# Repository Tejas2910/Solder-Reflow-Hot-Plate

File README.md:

# Solder-Reflow-Hot-Plate
## Course Project EE344: Electronic Design Lab

Project Details:
 -  Recipient of Best Project Award in the Electrical Engineering Department among 200+ students for creating Solder Reflow Hot Plate instrument to solder SMD components 
 -  Engineered a high-performance heating element reaching temperatures up to 300°C, a cooling mechanism capable
    of dropping temperatures at a maximum rate of 3°C/s, and a precision feedback circuit for temperature control
 -  Collaborated within a 3-member team to design an intuitive web interface for configuring reflow profiles, a user-
    friendly TFT LCD display for real-time information, a 3D-printed enclosure and PCB layouts using Eagle

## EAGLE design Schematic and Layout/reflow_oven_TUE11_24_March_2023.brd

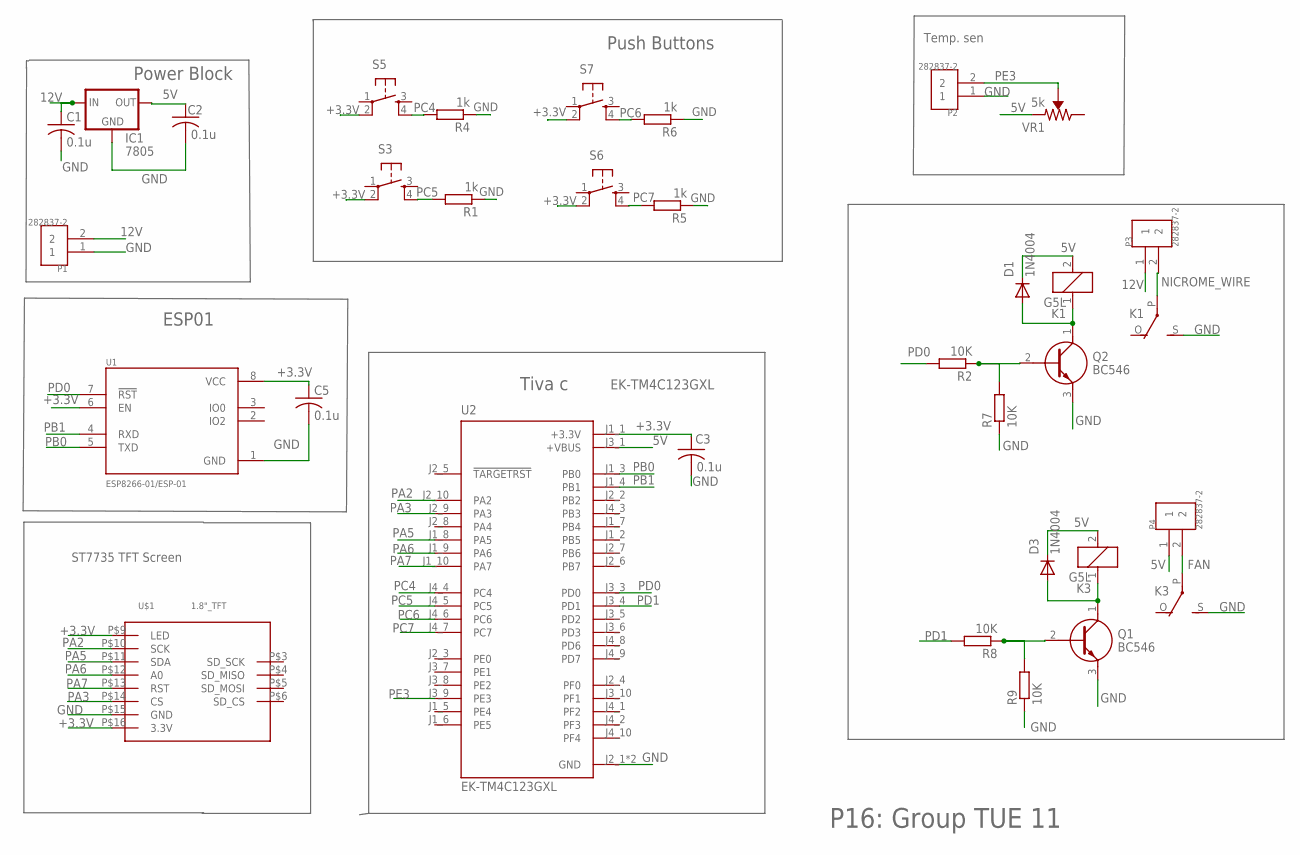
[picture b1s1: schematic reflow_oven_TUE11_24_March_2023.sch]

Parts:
C1, C2, C3, C5: 0.1u; C1206
D1, D3: 1N4004; DO41-10
IC1: 7805; 78XXS
K1, K3: G5L; G5LE
P1, P2, P3, P4: 282837-2; TE_282837-2
Q1, Q2: BC546
R1, R4, R5, R6: 1k; R1206
R2, R7, R8, R9: 10K; R1206
S3, S5, S6, S7: TAC_SWITCHPTH; TACTILE-PTH
U1: ESP8266-01/ESP-01; XCVR_ESP8266-01/ESP-01
U2: EK-TM4C123GXL; MODULE_EK-TM4C123GXL
U$1: 1.8"_TFT
VR1: 5k; TRIMPOT-PTH-3386U

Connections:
5V: C2.1, D1.C, D3.C, IC1.OUT, K1.2, K3.2, P4.1, U2.J3_1 (+VBUS), VR1.1 (CCW)
12V: C1.1, IC1.IN, P1.2, P3.1
+3.3V: C3.1, C5.1, S3.2, S5.2, S6.2, S7.2, U1.6 (EN), U1.8 (VCC), U2.J1_1 (+3.3V), U$1.P$9 (LED), U$1.P$16 (3.3V)
FAN: K3.P, P4.2
GND: C1.2, C2.2, C3.2, C5.2, IC1.GND, K1.S, K3.S, P1.1, P2.1, Q1.3 (E), Q2.3 (E), R1.1, R4.1, R5.1, R6.1, R7.1, R9.1, U1.1 (GND), U2.J2_1 (GND), U2.J3_2 (GND), U$1.P$15 (GND)
unnamed: Q2.2 (B), R2.1, R7.2
unnamed: D1.A, K1.1, Q2.1 (C)
unnamed: Q1.2 (B), R8.1, R9.2
unnamed: D3.A, K3.1, Q1.1 (C)
NICROME_WIRE: K1.P, P3.2
PA2: U2.J2_10 (PA2), U$1.P$10 (SCK)
PA3: U2.J2_9 (PA3), U$1.P$14 (CS)
PA5: U2.J1_8 (PA5), U$1.P$11 (SDA)
PA6: U2.J1_9 (PA6), U$1.P$12 (A0)
PA7: U2.J1_10 (PA7), U$1.P$13 (RST)
PB0: U1.5 (TXD), U2.J1_3 (PB0)
PB1: U1.4 (RXD), U2.J1_4 (PB1)
PC4: R4.2, S5.4, U2.J4_4 (PC4)
PC5: R1.2, S3.4, U2.J4_5 (PC5)
PC6: R6.2, S7.4, U2.J4_6 (PC6)
PC7: R5.2, S6.4, U2.J4_7 (PC7)
PD0: R2.2, U1.7 (!RST), U2.J3_3 (PD0)
PD1: R8.2, U2.J3_4 (PD1)
PE3: P2.2, U2.J3_9 (PE3), VR1.2 (WIPER)

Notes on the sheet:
Tiva c
ESP01
ST7735 TFT Screen
Temp. sen
Push Buttons
Power Block
P16: Group TUE 11
EK-TM4C123GXL

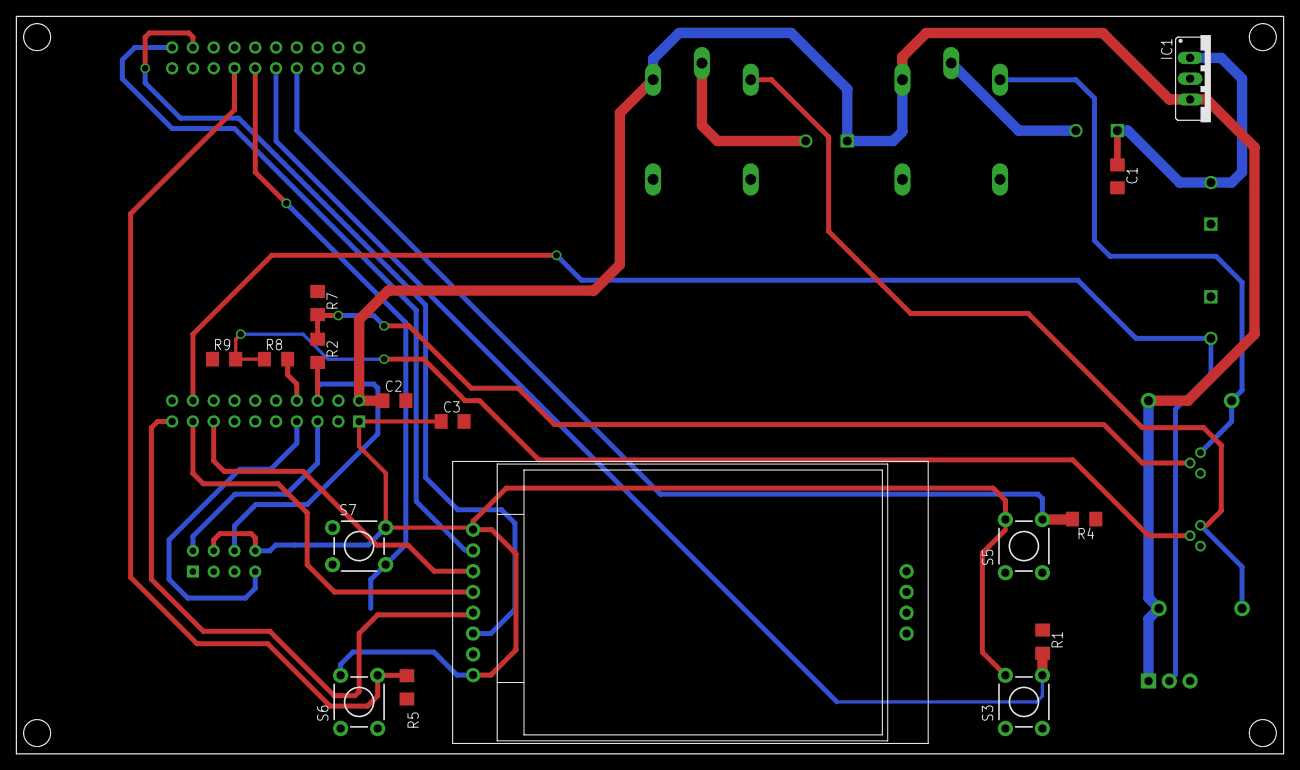
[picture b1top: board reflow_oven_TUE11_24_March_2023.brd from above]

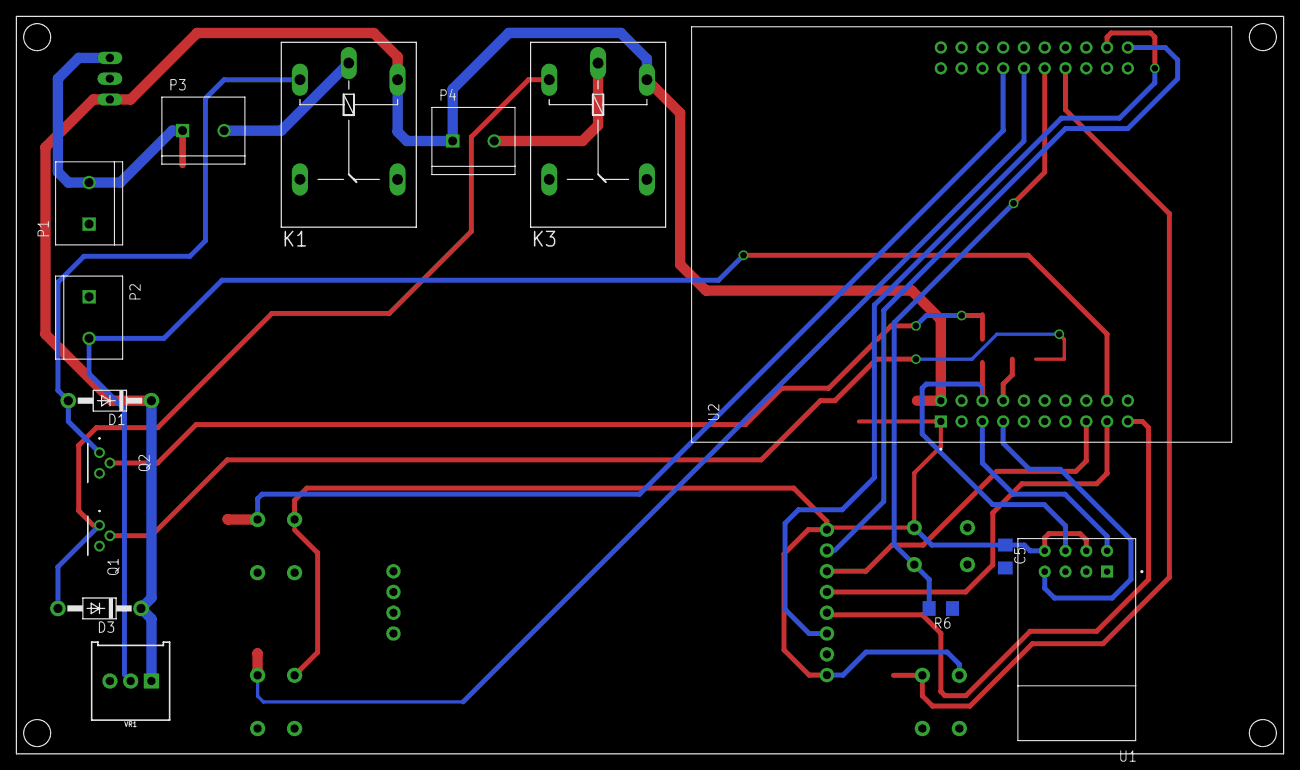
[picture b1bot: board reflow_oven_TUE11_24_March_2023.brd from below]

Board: 2 copper layers, 154.9 x 90.2 mm, 31 parts (15 on the bottom side), 24 nets.

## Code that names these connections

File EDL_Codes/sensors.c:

#include "myLib.h"
//----------------------------------------
// Prototypes
//----------------------------------------

// TO STORE THE VALUE IN VARIABLE ADC0Value FOR EVERY SAMPLING
uint32_t ADC0Value[1];

//---------------------------------------------------------------------------
// hardware_init()
//---------------------------------------------------------------------------
void relay_init(){
    SysCtlPeripheralEnable(SYSCTL_PERIPH_GPIOD);
    GPIOPinTypeGPIOOutput(GPIO_PORTD_BASE, GPIO_PIN_0 | GPIO_PIN_1);
}

// (pin PD0)-> nichrome wire,
// (pin PD1)-> fan\
// 1 -> only nichrome wire on and fan is off
// 2 -> nichrome wire in on and fan both on
// 3 -> only fan is on, nichrome is off
void relay_on(int number){
    if(number == 1){
        GPIOPinWrite(GPIO_PORTD_BASE, GPIO_PIN_0|GPIO_PIN_1, 0x01);
    }else if(number == 2){
        GPIOPinWrite(GPIO_PORTD_BASE, GPIO_PIN_0|GPIO_PIN_1, 0x03);
    }else if(number == 3){
        GPIOPinWrite(GPIO_PORTD_BASE, GPIO_PIN_0|GPIO_PIN_1, 0x02);
    }
}

void adc_init(void)
{
    //Set CPU Clock to 40MHz. 400MHz PLL/2 = 200 DIV 5 = 40MHz
    //SysCtlClockSet(SYSCTL_SYSDIV_5|SYSCTL_USE_PLL|SYSCTL_XTAL_16MHZ|SYSCTL_OSC_MAIN);

    // ADD Tiva-C GPIO setup -
    SysCtlPeripheralEnable(SYSCTL_PERIPH_ADC0); // ENABLE ADC0 MODUL
    SysCtlPeripheralEnable(SYSCTL_PERIPH_GPIOE); // ENABLE GPIO for ADC0 MODULE

    GPIOPinTypeADC(PORT_E,GPIO_PIN_3);// ENABLE AN0 OF ADC0 MODULE
    // ADC0 MODULE, TRIGGER IS PROCESSOR EVENT, SEQUENCER 0 IS CONFIGURED
    ADCSequenceConfigure(ADC_0, 1, ADC_TRIGGER_PROCESSOR, 0);

    // ADC0 MODULE, SEQUENCER 0 , FOR 1 SAMPLING, INPUT IS FROM CHANNEL 0 PE3
    ADCSequenceStepConfigure(ADC_0, 1, 0, ADC_CTL_CH0);
    // ENABLE THE SEQUENCE 1 FOR ADC0
    ADCSequenceEnable(ADC_0, 1);
}

int ADC_conv(void)
{
    // CLEAR INTERRUPT FLAG FOR ADC0, SEQUENCER 1
    ADCIntClear(ADC_0, 1);
    // TRIGGER IS GIVEN FOR ADC 0 MODULE, SEQUENCER 1
    ADCProcessorTrigger(ADC_0, 1);
    // STORE THE CONVERTED VALUE FOR ALL DIFFERENT SAMPLING IN ARRAY
    //ui32ADC0Value
    ADCSequenceDataGet(ADC_0, 1, ADC0Value);
    return ADC0Value[0];
}

float volt_to_resistor(ptvolt){
    float res_side = 120;
    float v_pow = 3.3;
    float v_adc = ptvolt*v_pow/4096;
    float v_high = 5;
    float resistor = res_side*v_adc*(v_high-v_adc);
    return v_adc*100;
}

int resistor_to_temp(float resistor){
    // 163 high high very
    // 160 la band karo -> 250 degree
    // 112 room temperature 28 degree
    int high_temp = 250;
    int room_temp = 28;
    int res_high = 160;
    int res_normal = 112;
    int temp;
    temp = 28+(resistor-res_normal)*(high_temp-room_temp)/(res_high-res_normal);
    return temp;
}

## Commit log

2023-09-03 Added codes, circuit layouts, STL files for 3D printing, report and some other details

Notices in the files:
parts and their libraries:
SparkFun-Retired: Licensing: Creative Commons ShareAlike 4.0 International - https://creativecommons.org/licenses/by-sa/4.0
